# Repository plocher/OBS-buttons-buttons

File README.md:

# OBS-buttons
## License: CERN Open Hardware Licence v1.2

Buttons Board for Arduino Keyboard Box

IO daughterboard with 3x SPDT momentary switches and a pushbutton

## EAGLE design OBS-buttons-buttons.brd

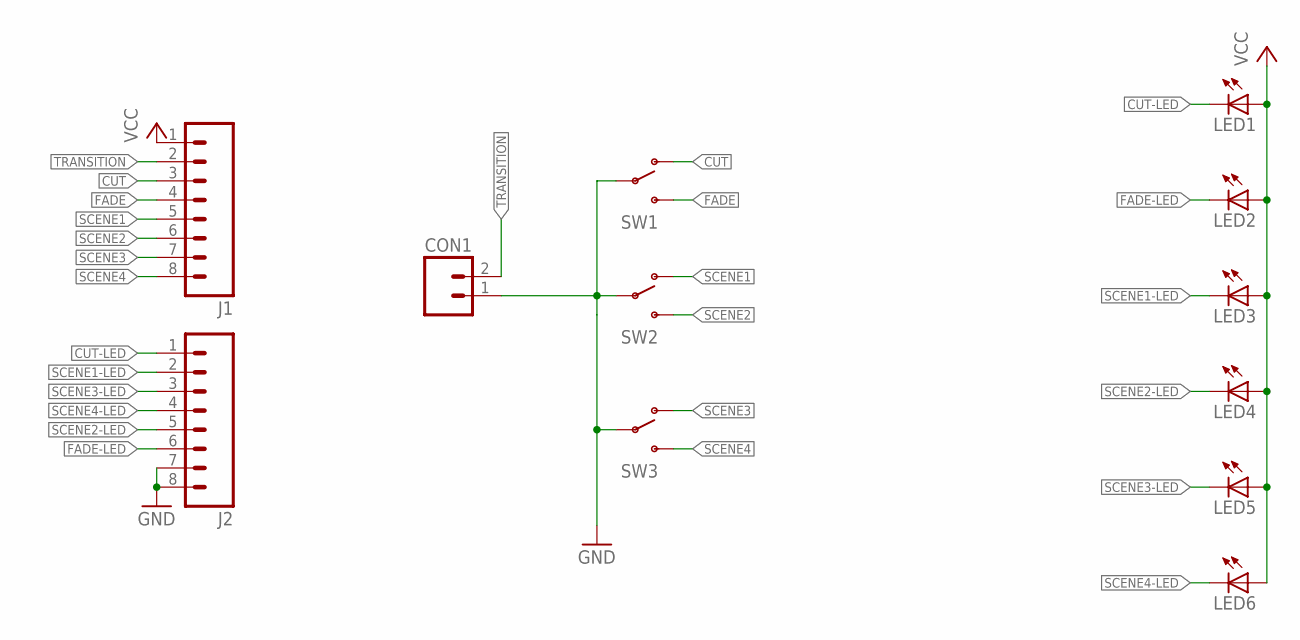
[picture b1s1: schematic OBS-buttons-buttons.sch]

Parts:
CON1: CONNECTOR-M02508-LOCK; MSTB2
J1, J2: CONNECTOR-M08LOCK; 1X08_LOCK
LED1, LED2, LED3, LED4, LED5, LED6: LEDLED5MM; LED5MM
SW1, SW2, SW3: SWITCH-SPSTPTH-508; SWITCH-SPDT-508

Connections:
CUT: J1.3, SW1.1 (O)
CUT-LED: J2.1, LED1.K (C)
FADE: J1.4, SW1.3 (S)
FADE-LED: J2.6, LED2.K (C)
GND: CON1.1 (A), J2.7, J2.8, SW1.2, SW2.2, SW3.2
SCENE1: J1.5, SW2.1 (O)
SCENE1-LED: J2.2, LED3.K (C)
SCENE2: J1.6, SW2.3 (S)
SCENE2-LED: J2.5, LED4.K (C)
SCENE3: J1.7, SW3.1 (O)
SCENE3-LED: J2.3, LED5.K (C)
SCENE4: J1.8, SW3.3 (S)
SCENE4-LED: J2.4, LED6.K (C)
TRANSITION: CON1.2 (B), J1.2
VCC: J1.1, LED1.A, LED2.A, LED3.A, LED4.A, LED5.A, LED6.A

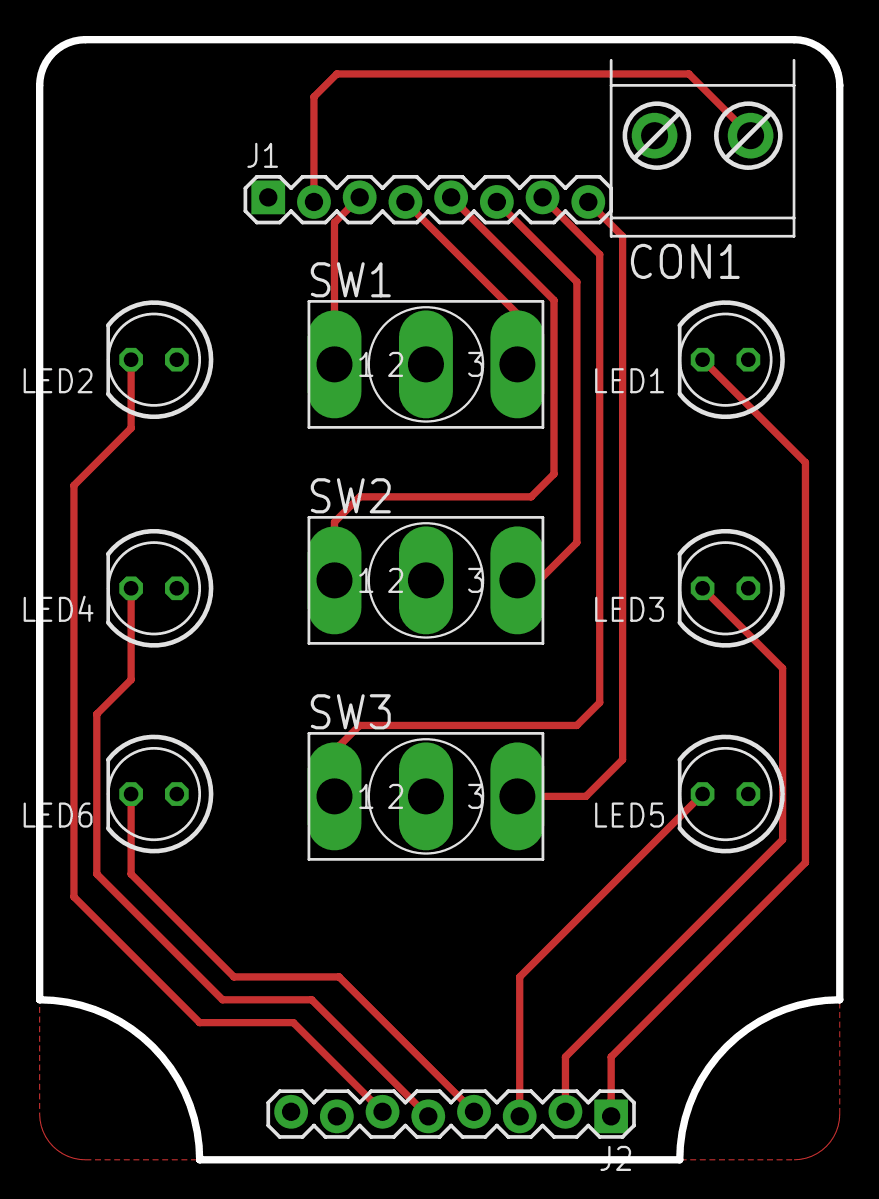
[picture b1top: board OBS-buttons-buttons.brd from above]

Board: 2 copper layers, 44.5 x 62.2 mm, 12 parts (0 on the bottom side), 15 nets.

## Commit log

2020-11-14 Initial version
2020-11-18 initial prototype
2020-11-28 bigger holes
